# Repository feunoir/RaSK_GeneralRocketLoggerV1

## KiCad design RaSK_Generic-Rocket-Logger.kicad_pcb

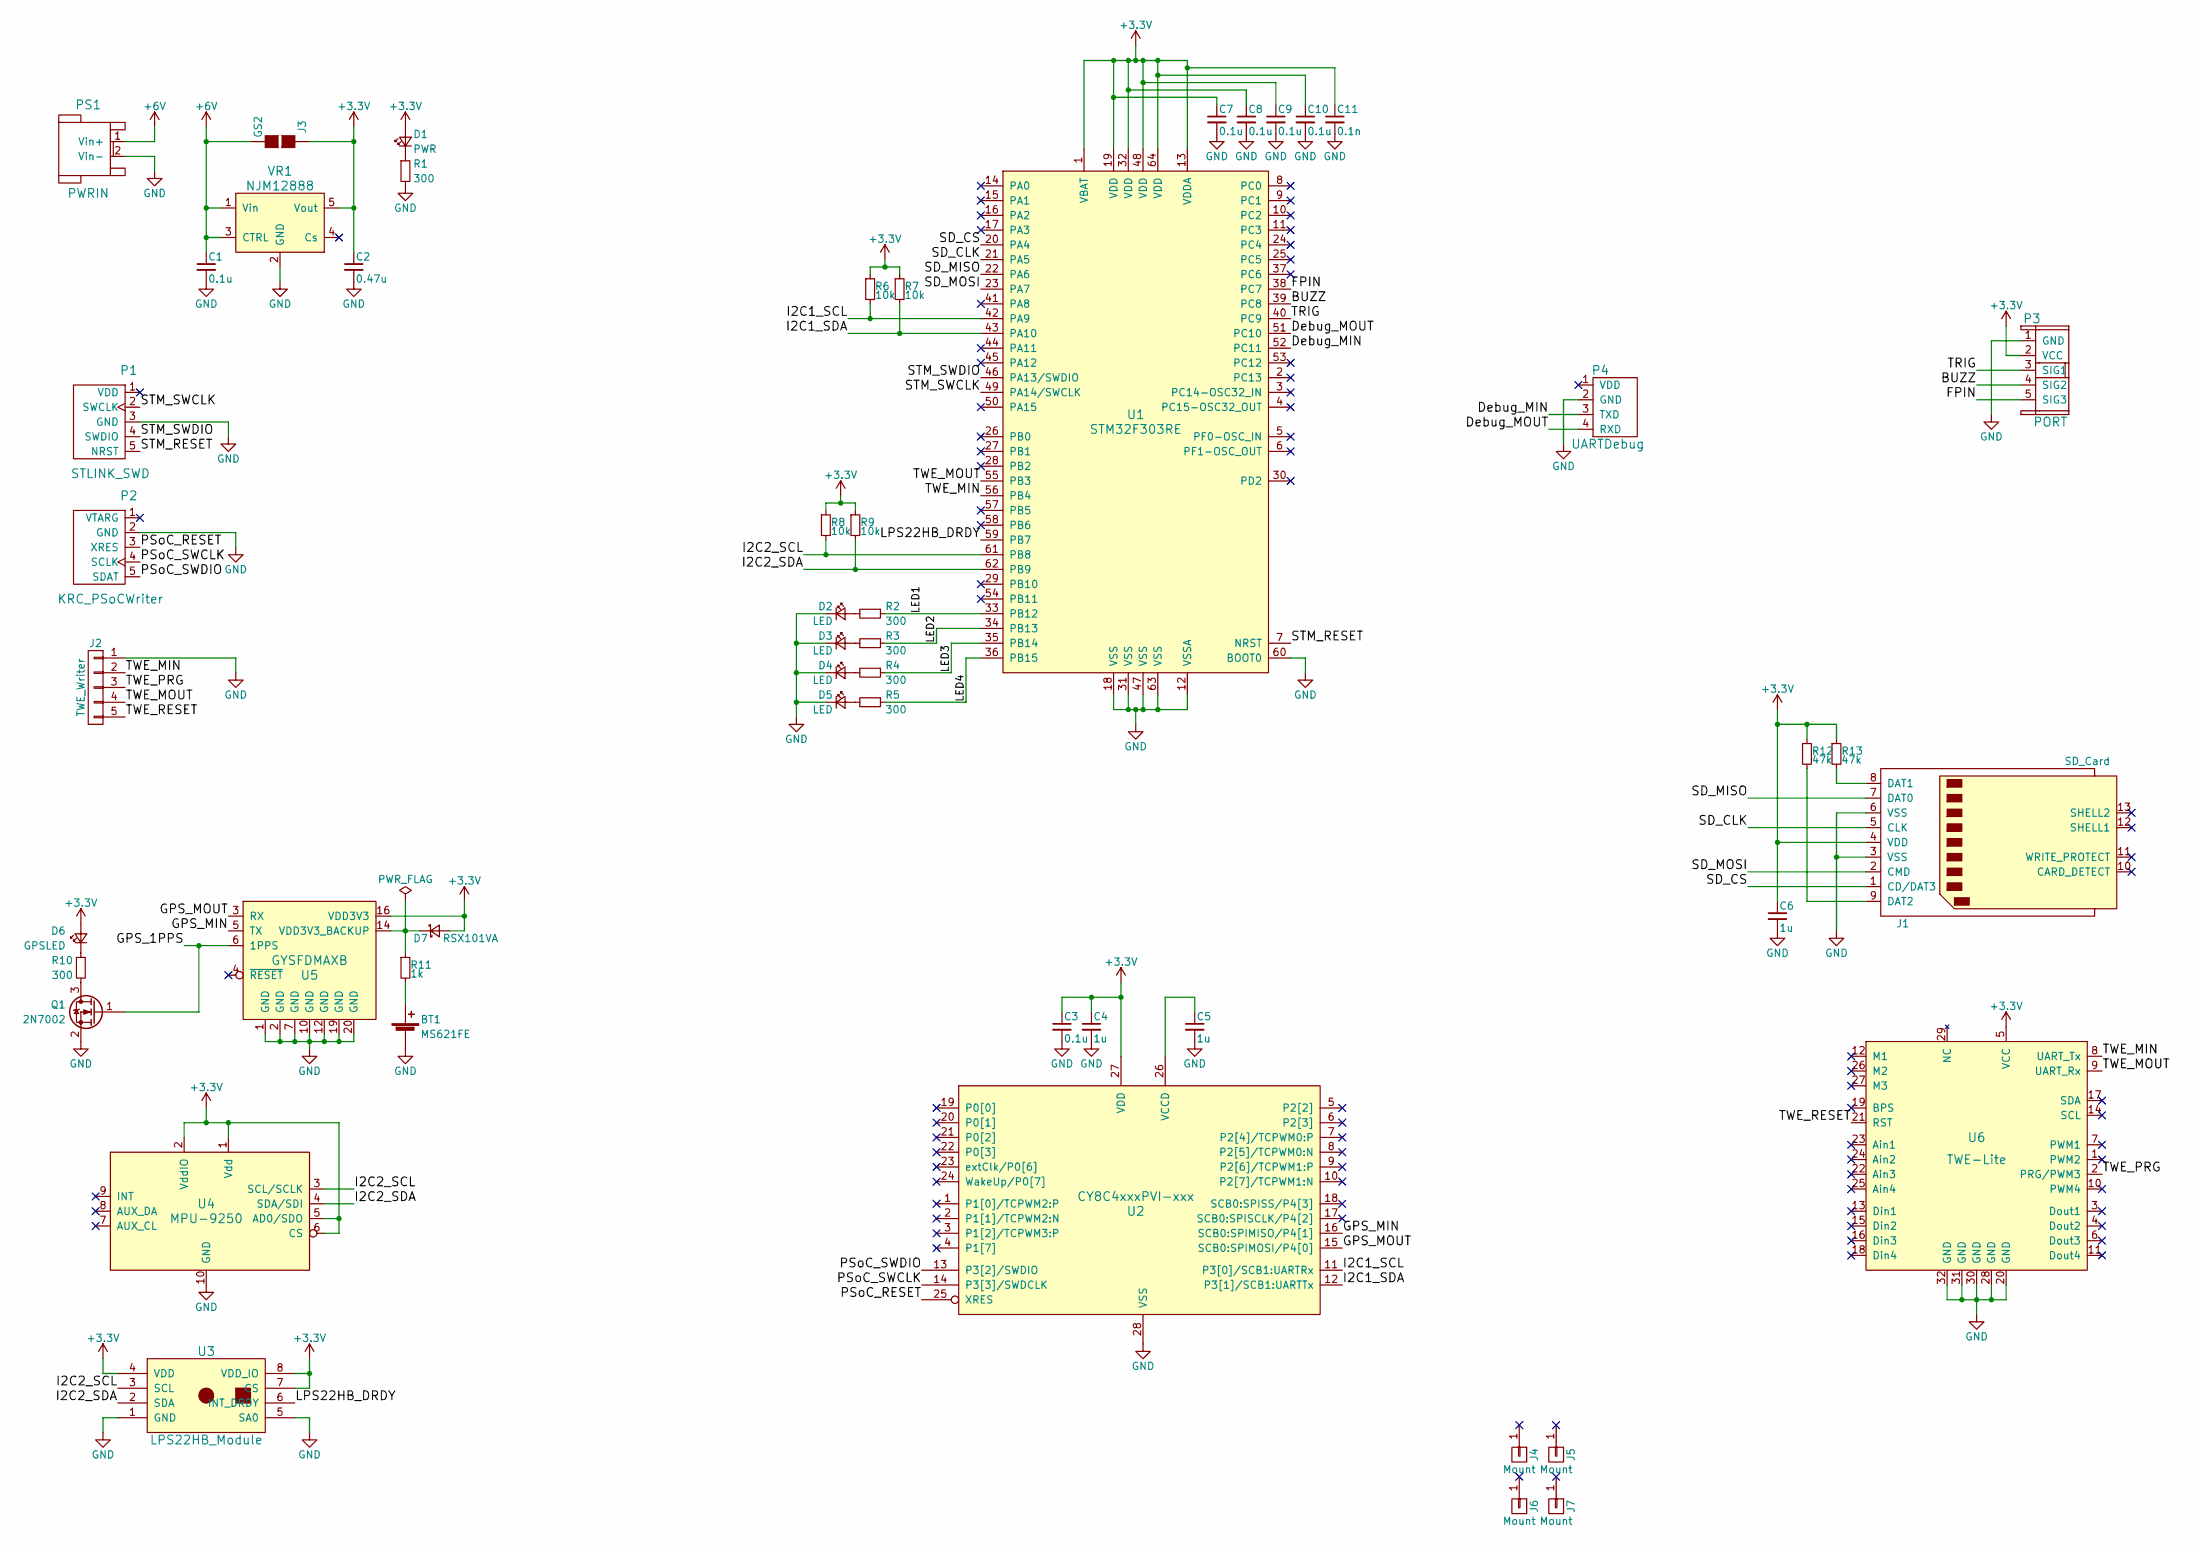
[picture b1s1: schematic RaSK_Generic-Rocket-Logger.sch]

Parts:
BT1: MS621FE; E-Type_D6.8
C1, C3, C7, C8, C9, C10: 0.1u; C_0603
C2: 0.47u; C_0603
C4, C5, C6: 1u; C_0603
C11: 0.1n; C_0603
D1: PWR; LED_0603
D2, D3, D4, D5: LED; LED_0603
D6: GPSLED; LED_0603
D7: RSX101VA; D_TUMD2
J1: SD_Card; microSD_DM3AT-SFPEJ
J2: TWE_Writer; DF3DZ-5P-2V
J3: GS2
J4, J5, J6, J7: Mount; MountingHole_3mm
P1: STLINK_SWD; DF3DZ-5P-2V
P2: KRC_PSoCWriter; DF3DZ-5P-2V
P3: PORT; DF3A-5P-2DSA
P4: UARTDebug; Pin_Header_Straight_1x04_Pitch2.54mm
PS1: PWRIN; DF3A-2P-2DSA
Q1: 2N7002; SOT-23
R1, R2, R3, R4, R5, R10: 300; R_0603
R6, R7, R8, R9: 10k; R_0603
R11: 1k; R_0603
R12, R13: 47k; R_0603
U1: STM32F303RE; LQFP-64_10x10mm_Pitch0.5mm
U2: CY8C4xxxPVI-xxx; SSOP-28_5.3x10.2mm_Pitch0.65mm
U3: LPS22HB_Module; Strawberry-Linux_Module_8P_NoHole
U4: MPU-9250; DIP-10_W7.62mm
U5: GYSFDMAXB; GYSFDMAXB_2Hole
U6: TWE-Lite
VR1: NJM12888; SOT-23-5

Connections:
+3V3: C2.1, C3.1, C4.1, C6.1, C7.1, C8.1, C9.1, C10.1, C11.1, D1.2 (A), D6.2 (A), D7.2 (A), J1.4 (VDD), J3.1 (G1), P3.2 (VCC), R6.1, R7.1, R8.1, R9.1, R12.1, R13.1, U1.1 (VBAT), U1.13 (VDDA), U1.19 (VDD), U1.32 (VDD), U1.48 (VDD), U1.64 (VDD), U2.27 (VDD), U3.4 (VDD), U3.7 (CS), U3.8 (VDD_IO), U4.1 (Vdd), U4.2 (VddIO), U4.5 (AD0/SDO), U4.6 (CS), U5.16 (VDD3V3), U6.5 (VCC), VR1.5 (Vout)
+6V: C1.1, J3.2 (G2), PS1.1 (Vin+), VR1.1 (Vin), VR1.3 (CTRL)
/BUZZ: P3.4 (SIG2), U1.39 (PC8)
/Debug_MIN: P4.3 (TXD), U1.52 (PC11)
/Debug_MOUT: P4.4 (RXD), U1.51 (PC10)
/FPIN: P3.5 (SIG3), U1.38 (PC7)
/GPS_1PPS: Q1.1 (G), U5.6 (1PPS)
/GPS_MIN: U2.16 (SCB0:SPIMISO/P4[1]), U5.5 (TX)
/GPS_MOUT: U2.15 (SCB0:SPIMOSI/P4[0]), U5.3 (RX)
/I2C1_SCL: R6.2, U1.42 (PA9), U2.11 (P3[0]/SCB1:UARTRx)
/I2C1_SDA: R7.2, U1.43 (PA10), U2.12 (P3[1]/SCB1:UARTTx)
/I2C2_SCL: R8.2, U1.61 (PB8), U3.3 (SCL), U4.3 (SCL/SCLK)
/I2C2_SDA: R9.2, U1.62 (PB9), U3.2 (SDA), U4.4 (SDA/SDI)
/LED1: R2.1, U1.33 (PB12)
/LED2: R3.1, U1.34 (PB13)
/LED3: R4.1, U1.35 (PB14)
/LED4: R5.1, U1.36 (PB15)
/LPS22HB_DRDY: U1.59 (PB7), U3.6 (INT_DRDY)
/PSoC_RESET: P2.3 (XRES), U2.25 (XRES)
/PSoC_SWCLK: P2.4 (SCLK), U2.14 (P3[3]/SWDCLK)
/PSoC_SWDIO: P2.5 (SDAT), U2.13 (P3[2]/SWDIO)
/SD_CLK: J1.5 (CLK), U1.21 (PA5)
/SD_CS: J1.1 (CD/DAT3), U1.20 (PA4)
/SD_MISO: J1.7 (DAT0), U1.22 (PA6)
/SD_MOSI: J1.2 (CMD), U1.23 (PA7)
/STM_RESET: P1.5 (NRST), U1.7 (NRST)
/STM_SWCLK: P1.2 (SWCLK), U1.49 (PA14/SWCLK)
/STM_SWDIO: P1.4 (SWDIO), U1.46 (PA13/SWDIO)
/TRIG: P3.3 (SIG1), U1.40 (PC9)
/TWE_MIN: J2.2, U1.56 (PB4), U6.8 (UART_Tx)
/TWE_MOUT: J2.4, U1.55 (PB3), U6.9 (UART_Rx)
/TWE_PRG: J2.3, U6.2 (PRG/PWM3)
/TWE_RESET: J2.5, U6.21 (RST)
GND: BT1.2 (-), C1.2, C2.2, C3.2, C4.2, C5.2, C6.2, C7.2, C8.2, C9.2, C10.2, C11.2, D2.1 (K), D3.1 (K), D4.1 (K), D5.1 (K), J1.3 (VSS), J1.6 (VSS), J2.1, P1.3 (GND), P2.2 (GND), P3.1 (GND), P4.2 (GND), PS1.2 (Vin-), Q1.2 (S), R1.2, U1.12 (VSSA), U1.18 (VSS), U1.31 (VSS), U1.47 (VSS), U1.60 (BOOT0), U1.63 (VSS), U2.28 (VSS), U3.1 (GND), U3.5 (SA0), U4.10 (GND), U5.1 (GND), U5.2 (GND), U5.7 (GND), U5.10 (GND), U5.12 (GND), U5.19 (GND), U5.20 (GND), U6.20 (GND), U6.28 (GND), U6.30 (GND), U6.31 (GND), U6.32 (GND), VR1.2 (GND)
unnamed: BT1.1 (+), R11.2
unnamed: C5.1, U2.26 (VCCD)
unnamed: D1.1 (K), R1.1
unnamed: D2.2 (A), R2.2
unnamed: D3.2 (A), R3.2
unnamed: D4.2 (A), R4.2
unnamed: D5.2 (A), R5.2
unnamed: D6.1 (K), R10.1
unnamed: D7.1 (K), R11.1, U5.14 (VDD3V3_BACKUP)
unnamed: J1.8 (DAT1), R13.2
unnamed: J1.9 (DAT2), R12.2
unnamed: Q1.3 (D), R10.2

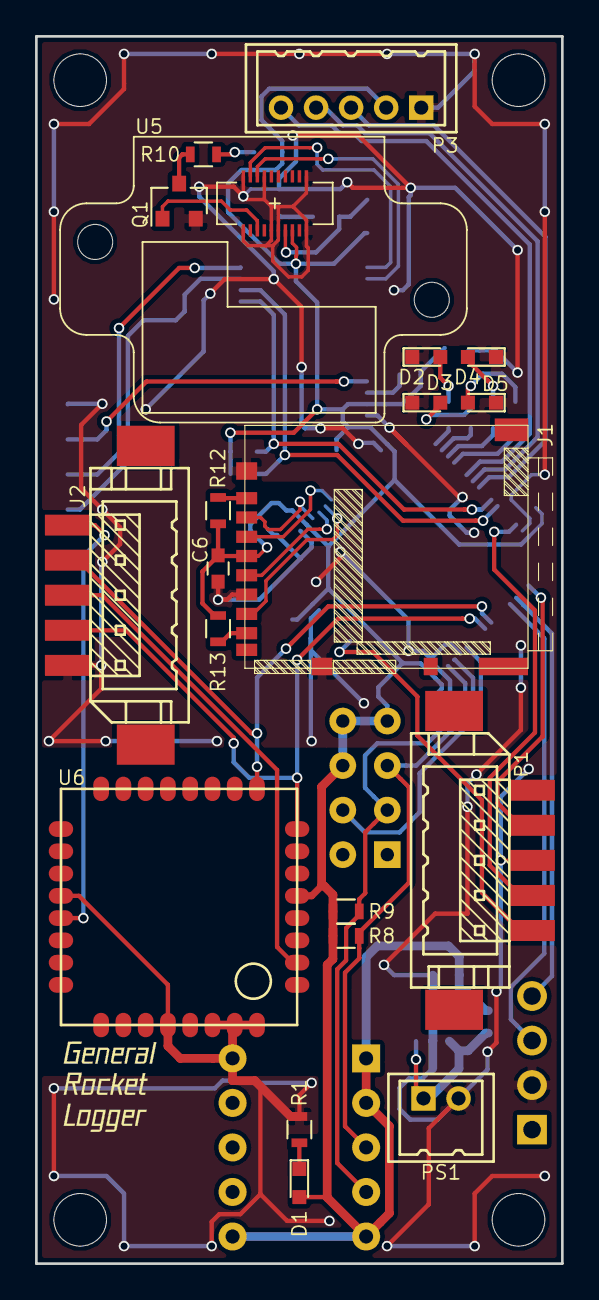
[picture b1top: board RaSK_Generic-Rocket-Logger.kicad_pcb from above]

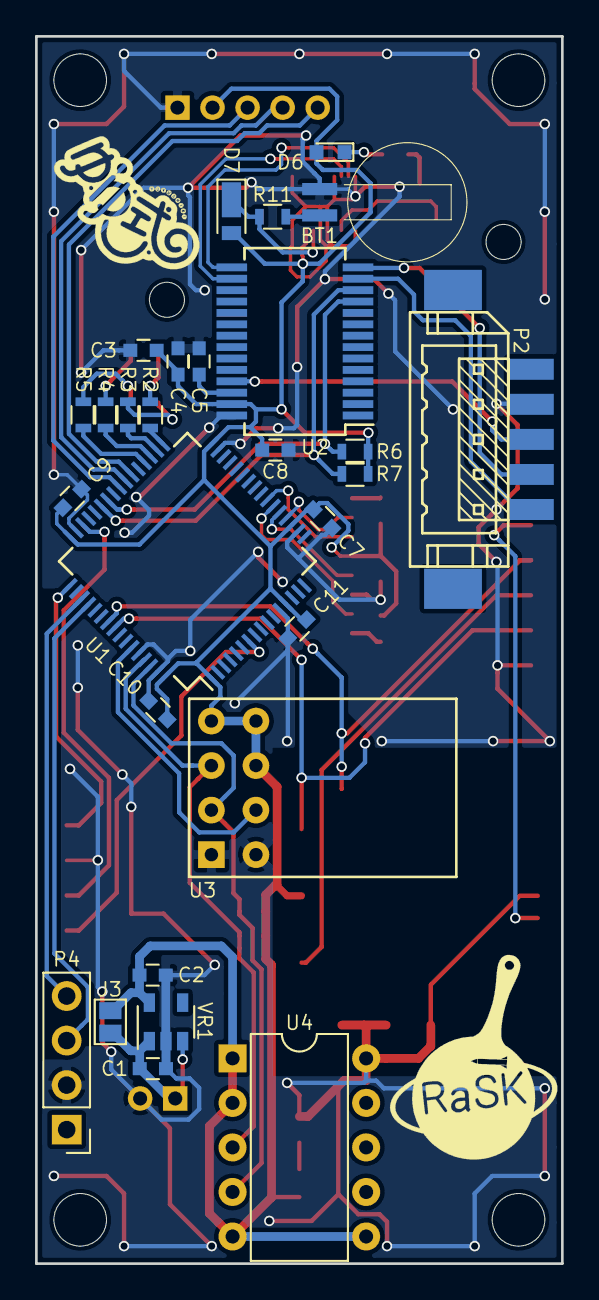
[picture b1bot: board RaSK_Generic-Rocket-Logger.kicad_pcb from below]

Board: 2 copper layers, 30.0 x 70.0 mm, 52 parts (28 on the bottom side), 46 nets.

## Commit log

2017-07-02 :circus_tent: Added .gitattributes & .gitignore files
2017-07-02 add kut-kicad library
2017-07-02 Project initialization
    create kicad project
2017-07-02 connect library to project
2017-07-02 update library
2017-07-02 add component lps22hb
2017-08-07 editing schematic is completed
2017-08-07 complete board drawing
2017-08-08 some modification library
2017-08-13 add buzzer out and trigger pin to port
2017-09-22 board released
    とりあえず完成品
